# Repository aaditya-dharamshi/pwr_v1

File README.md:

# pwr_v1
Main powerboard (first version) PCB files.

This was the first major board designed for SeeGoals, a project under FIA Robotics at Linkoping University, Sweden. I designed the complete PCB (assisted by other teammates who have developed the foundation), and the design files are shared here with permission from LiU SeeGoals.

This was the prototype for the main power distribution and interface board for the robot, powered by a 23.8V LiPo battery. This board is designed with KiCAD 8, and this repository contains the KiCAD project files and related documents.

# Documentations
📄 [Schematic PDF](Docs%20and%20Images/pwr_v1_schematic.pdf)
📄 [Layout PDF ](Docs%20and%20Images/pwr_v1_CopperLayers.pdf)

# 3D renders
Top view

Bottom view

Main features:
- 3.3V, 5V and 12V buck converters
- IMU on board
- Interfaces for STM32 Nucleo, nRF board and kicker board.

Stackup: 
- 4-layer FR4 PCB with 1.6mm thickness
- Copper thickness: 2 oz outer layer and 1 oz inner layers.

Design considerations:
- High-current power distribution from the LiPo battery.
- Dedicated power and signal layers.
- 4-layered stackup for improved grounding and power integrity.
- Decoupling capacitors placed carefully near the components.
- SMD-type connectors used for STM32 Nucleo interface, reducing thru hole pins and enabling better power and ground plane integrity.

Validation	
- This board was fabricated, assembled and integrated into the robot.
- During validation, issues related to nRF connector pin mapping, connector selection and mechanical design perspectivewere identified, which were addressed in the second revision.

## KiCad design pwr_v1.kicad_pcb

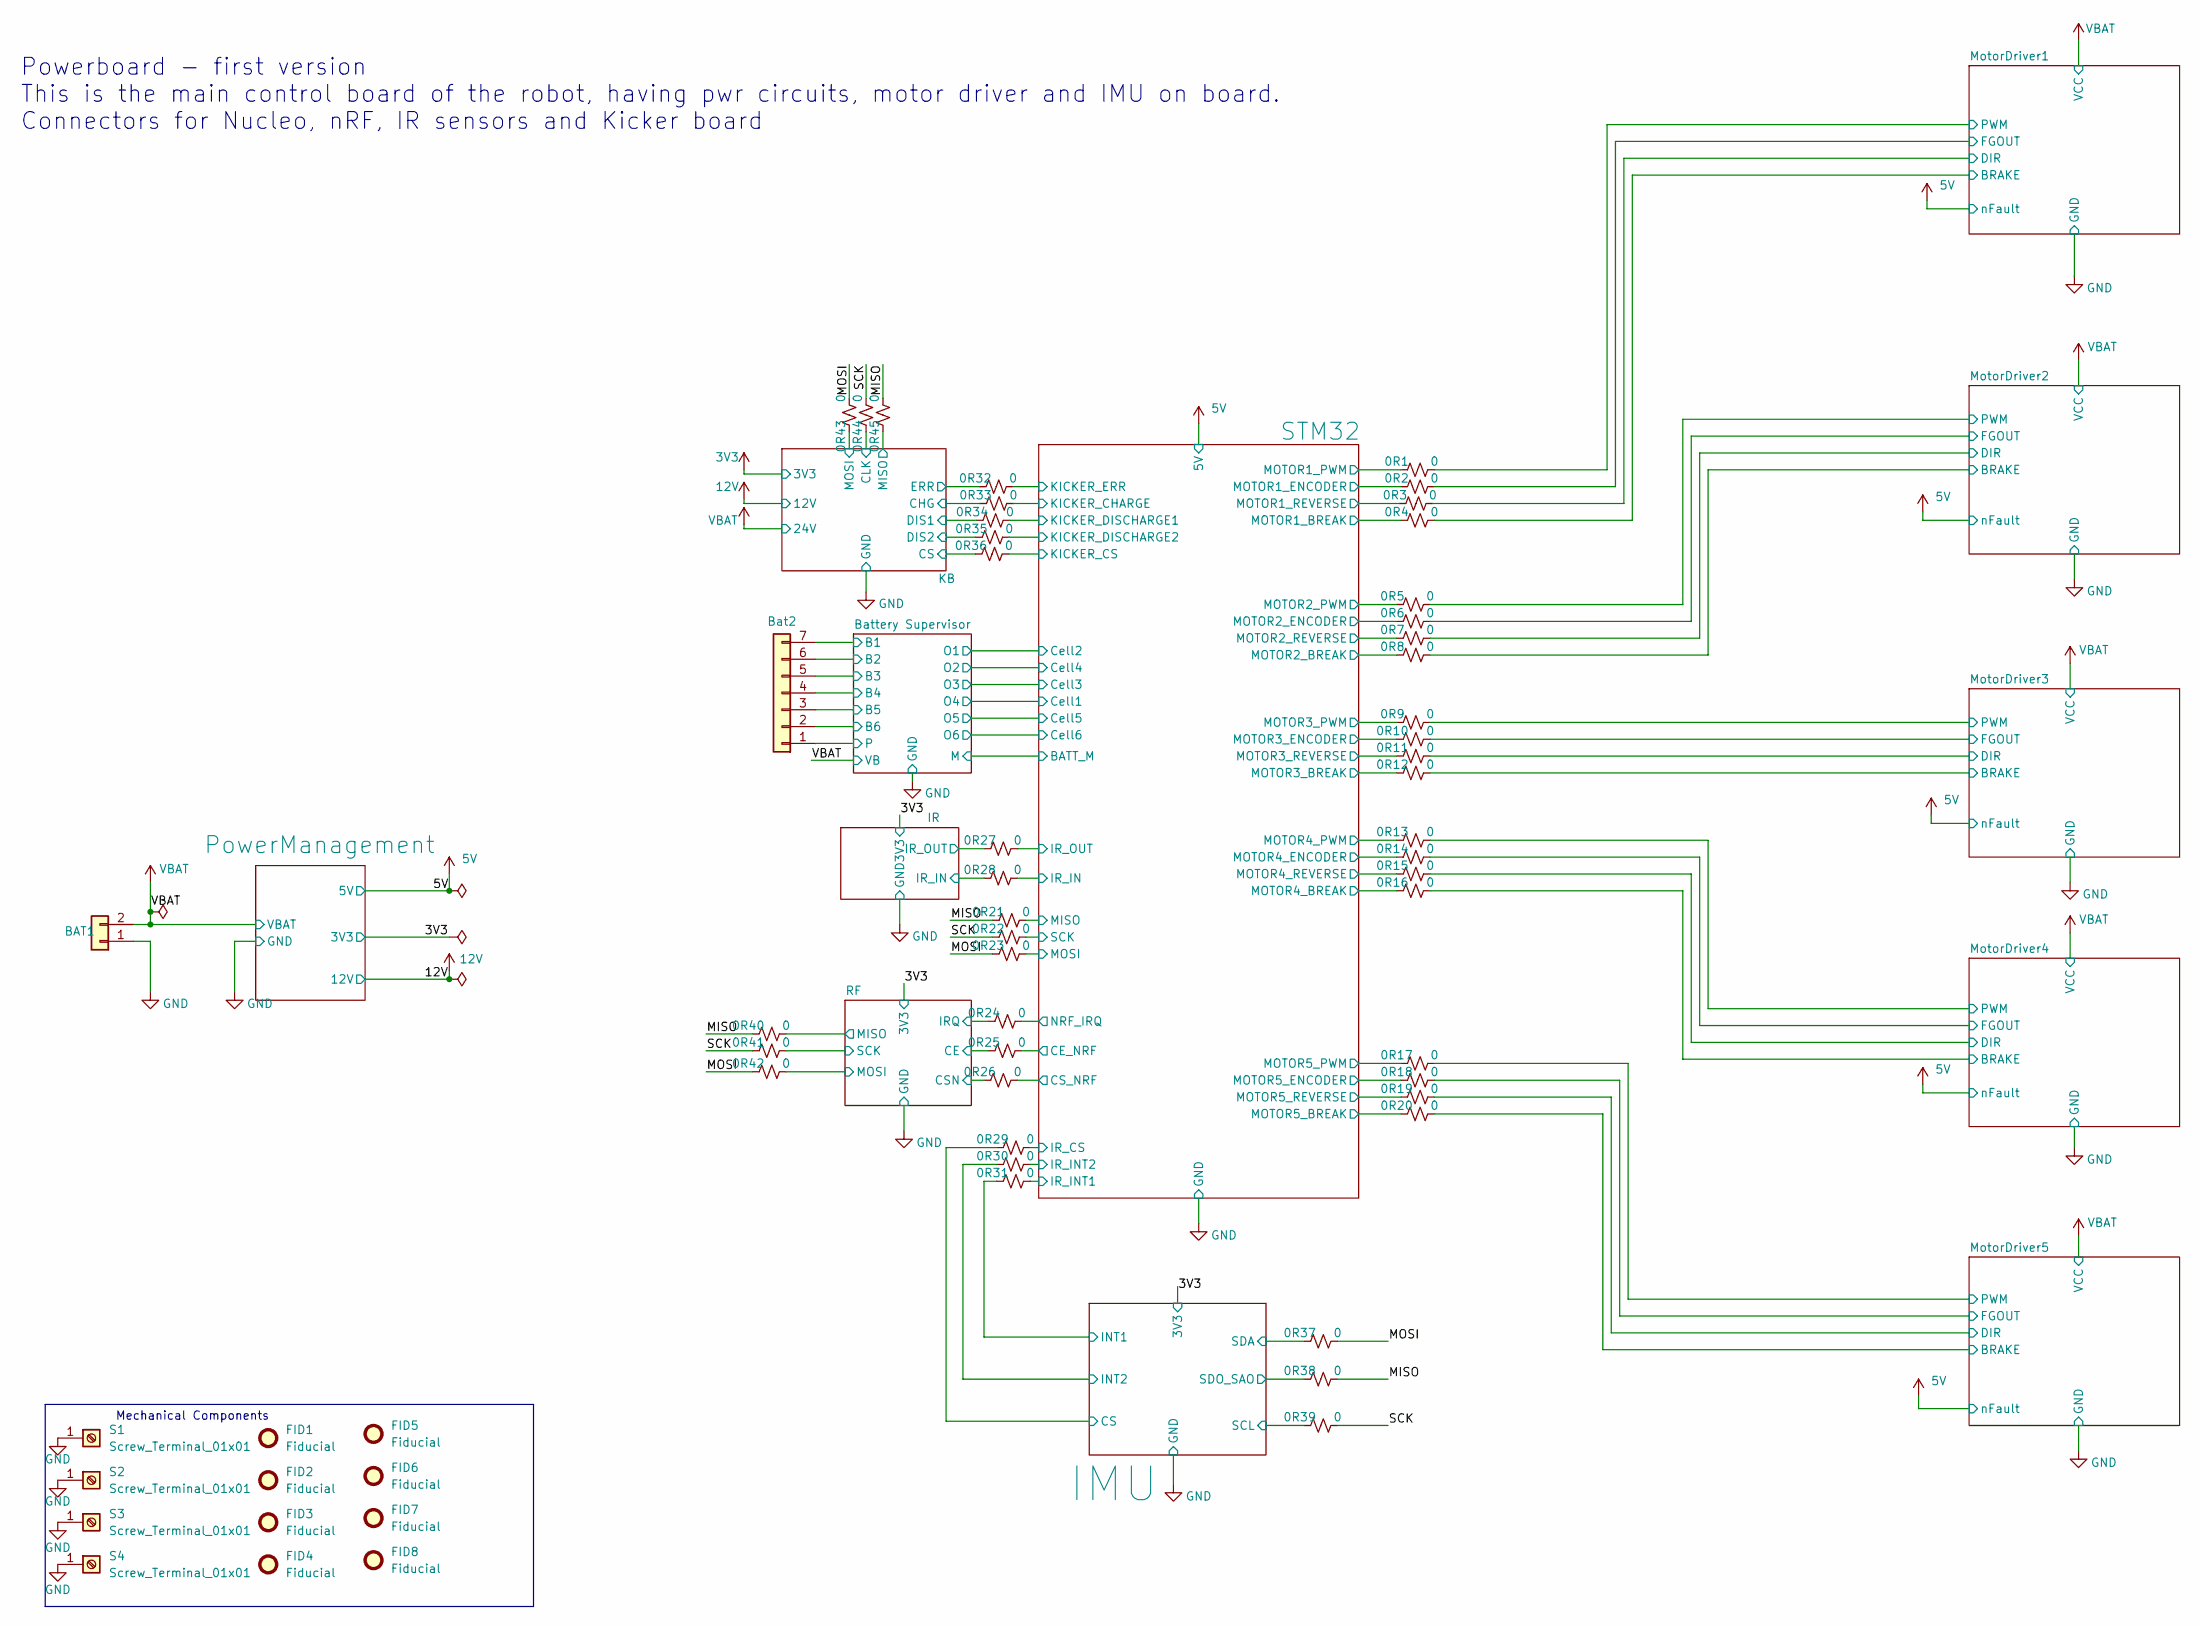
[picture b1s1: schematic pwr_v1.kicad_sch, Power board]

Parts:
0R1, 0R2, 0R3, 0R4, 0R5, 0R6, 0R7, 0R8, 0R9, 0R10, 0R11, 0R12, 0R13, 0R14, 0R15, 0R16, 0R17, 0R18, 0R19, 0R20, 0R21, 0R22, 0R23, 0R24, 0R25, 0R26, 0R27, 0R28, 0R29, 0R30, 0R31, 0R32, 0R33, 0R34, 0R35, 0R36, 0R37, 0R38, 0R39, 0R40, 0R41, 0R42, 0R43, 0R44, 0R45: 0; R_0603_1608Metric
BAT1: XT60; AMASS_XT60-M_1x02_P7.20mm_Vertical
Bat2: Conn_01x07; JST_B7B-XH-A
FID1, FID2, FID3, FID4, FID5, FID6, FID7, FID8: Fiducial; Fiducial_1mm_Mask3mm
S1, S2, S3, S4: Screw_Terminal_01x01; TerminalBlock_MetzConnect_360271_1x01_Horizontal_ScrewM3.0_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

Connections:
/Battery Supervisor/B1: Bat2.7; also elsewhere on the board
/Battery Supervisor/B2: Bat2.6; also elsewhere on the board
/Battery Supervisor/B3: Bat2.5; also elsewhere on the board
/Battery Supervisor/B4: Bat2.4; also elsewhere on the board
/Battery Supervisor/B5: Bat2.3; also elsewhere on the board
/Battery Supervisor/B6: Bat2.2; also elsewhere on the board
/Battery Supervisor/P: Bat2.1; also elsewhere on the board
/IMU/CS: 0R29.1; also elsewhere on the board
/IMU/INT1: 0R31.1; also elsewhere on the board
/IMU/INT2: 0R30.1; also elsewhere on the board
/IMU/SCL: 0R39.1; also elsewhere on the board
/IMU/SDA: 0R37.1; also elsewhere on the board
/IMU/SDO_SAO: 0R38.1; also elsewhere on the board
/IR/IR_IN: 0R28.1; also elsewhere on the board
/IR/IR_OUT: 0R27.1; also elsewhere on the board
/KB/CHG: 0R33.1; also elsewhere on the board
/KB/CLK: 0R44.1; also elsewhere on the board
/KB/CS: 0R36.1; also elsewhere on the board
/KB/DIS1: 0R34.1; also elsewhere on the board
/KB/DIS2: 0R35.1; also elsewhere on the board
/KB/ERR: 0R32.1; also elsewhere on the board
/KB/MISO: 0R45.1; also elsewhere on the board
/KB/MOSI: 0R43.1; also elsewhere on the board
/MISO: 0R21.1, 0R38.2, 0R40.1, 0R45.2
/MOSI: 0R23.1, 0R37.2, 0R42.1, 0R43.2
/MotorDriver1/BRAKE: 0R4.2; also elsewhere on the board
/MotorDriver1/DIR: 0R3.2; also elsewhere on the board
/MotorDriver1/FGOUT: 0R2.2; also elsewhere on the board
/MotorDriver1/PWM: 0R1.2; also elsewhere on the board
/MotorDriver2/BRAKE: 0R8.2; also elsewhere on the board
/MotorDriver2/DIR: 0R7.2; also elsewhere on the board
/MotorDriver2/FGOUT: 0R6.2; also elsewhere on the board
/MotorDriver2/PWM: 0R5.2; also elsewhere on the board
/MotorDriver3/BRAKE: 0R12.2; also elsewhere on the board
/MotorDriver3/DIR: 0R11.2; also elsewhere on the board
/MotorDriver3/FGOUT: 0R10.2; also elsewhere on the board
/MotorDriver3/PWM: 0R9.2; also elsewhere on the board
/MotorDriver4/BRAKE: 0R16.2; also elsewhere on the board
/MotorDriver4/DIR: 0R15.2; also elsewhere on the board
/MotorDriver4/FGOUT: 0R14.2; also elsewhere on the board
/MotorDriver4/PWM: 0R13.2; also elsewhere on the board
/MotorDriver5/BRAKE: 0R20.2; also elsewhere on the board
/MotorDriver5/DIR: 0R19.2; also elsewhere on the board
/MotorDriver5/FGOUT: 0R18.2; also elsewhere on the board
/MotorDriver5/PWM: 0R17.2; also elsewhere on the board
/RF/CE: 0R25.1; also elsewhere on the board
/RF/CSN: 0R26.1; also elsewhere on the board
/RF/IRQ: 0R24.1; also elsewhere on the board
/RF/MISO: 0R40.2; also elsewhere on the board
/RF/MOSI: 0R42.2; also elsewhere on the board
/RF/SCK: 0R41.2; also elsewhere on the board
/SCK: 0R22.1, 0R39.2, 0R41.1, 0R44.2
/STM32/CE_NRF: 0R25.2; also elsewhere on the board
/STM32/CS_NRF: 0R26.2; also elsewhere on the board
/STM32/IR_CS: 0R29.2; also elsewhere on the board
/STM32/IR_IN: 0R28.2; also elsewhere on the board
/STM32/IR_INT1: 0R31.2; also elsewhere on the board
/STM32/IR_INT2: 0R30.2; also elsewhere on the board
/STM32/IR_OUT: 0R27.2; also elsewhere on the board
/STM32/KICKER_CHARGE: 0R33.2; also elsewhere on the board
/STM32/KICKER_CS: 0R36.2; also elsewhere on the board
/STM32/KICKER_DISCHARGE1: 0R34.2; also elsewhere on the board
/STM32/KICKER_DISCHARGE2: 0R35.2; also elsewhere on the board
/STM32/KICKER_ERR: 0R32.2; also elsewhere on the board
/STM32/MISO: 0R21.2; also elsewhere on the board
/STM32/MOSI: 0R23.2; also elsewhere on the board
/STM32/MOTOR1_BREAK: 0R4.1; also elsewhere on the board
/STM32/MOTOR1_ENCODER: 0R2.1; also elsewhere on the board
/STM32/MOTOR1_PWM: 0R1.1; also elsewhere on the board
/STM32/MOTOR1_REVERSE: 0R3.1; also elsewhere on the board
/STM32/MOTOR2_BREAK: 0R8.1; also elsewhere on the board
/STM32/MOTOR2_ENCODER: 0R6.1; also elsewhere on the board
/STM32/MOTOR2_PWM: 0R5.1; also elsewhere on the board
/STM32/MOTOR2_REVERSE: 0R7.1; also elsewhere on the board
/STM32/MOTOR3_BREAK: 0R12.1; also elsewhere on the board
/STM32/MOTOR3_ENCODER: 0R10.1; also elsewhere on the board
/STM32/MOTOR3_PWM: 0R9.1; also elsewhere on the board
/STM32/MOTOR3_REVERSE: 0R11.1; also elsewhere on the board
/STM32/MOTOR4_BREAK: 0R16.1; also elsewhere on the board
/STM32/MOTOR4_ENCODER: 0R14.1; also elsewhere on the board
/STM32/MOTOR4_PWM: 0R13.1; also elsewhere on the board
/STM32/MOTOR4_REVERSE: 0R15.1; also elsewhere on the board
/STM32/MOTOR5_BREAK: 0R20.1; also elsewhere on the board
/STM32/MOTOR5_ENCODER: 0R18.1; also elsewhere on the board
/STM32/MOTOR5_PWM: 0R17.1; also elsewhere on the board
/STM32/MOTOR5_REVERSE: 0R19.1; also elsewhere on the board
/STM32/NRF_IRQ: 0R24.2; also elsewhere on the board
/STM32/SCK: 0R22.2; also elsewhere on the board
GND: BAT1.1, S1.1, S2.1, S3.1, S4.1; also elsewhere on the board
VBAT: BAT1.2; also elsewhere on the board

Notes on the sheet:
Mechanical Components
Powerboard - first version This is the main control board of the robot, having pwr circuits, motor driver and IMU on board. Connectors for Nucleo, nRF, IR sensors and Kicker board

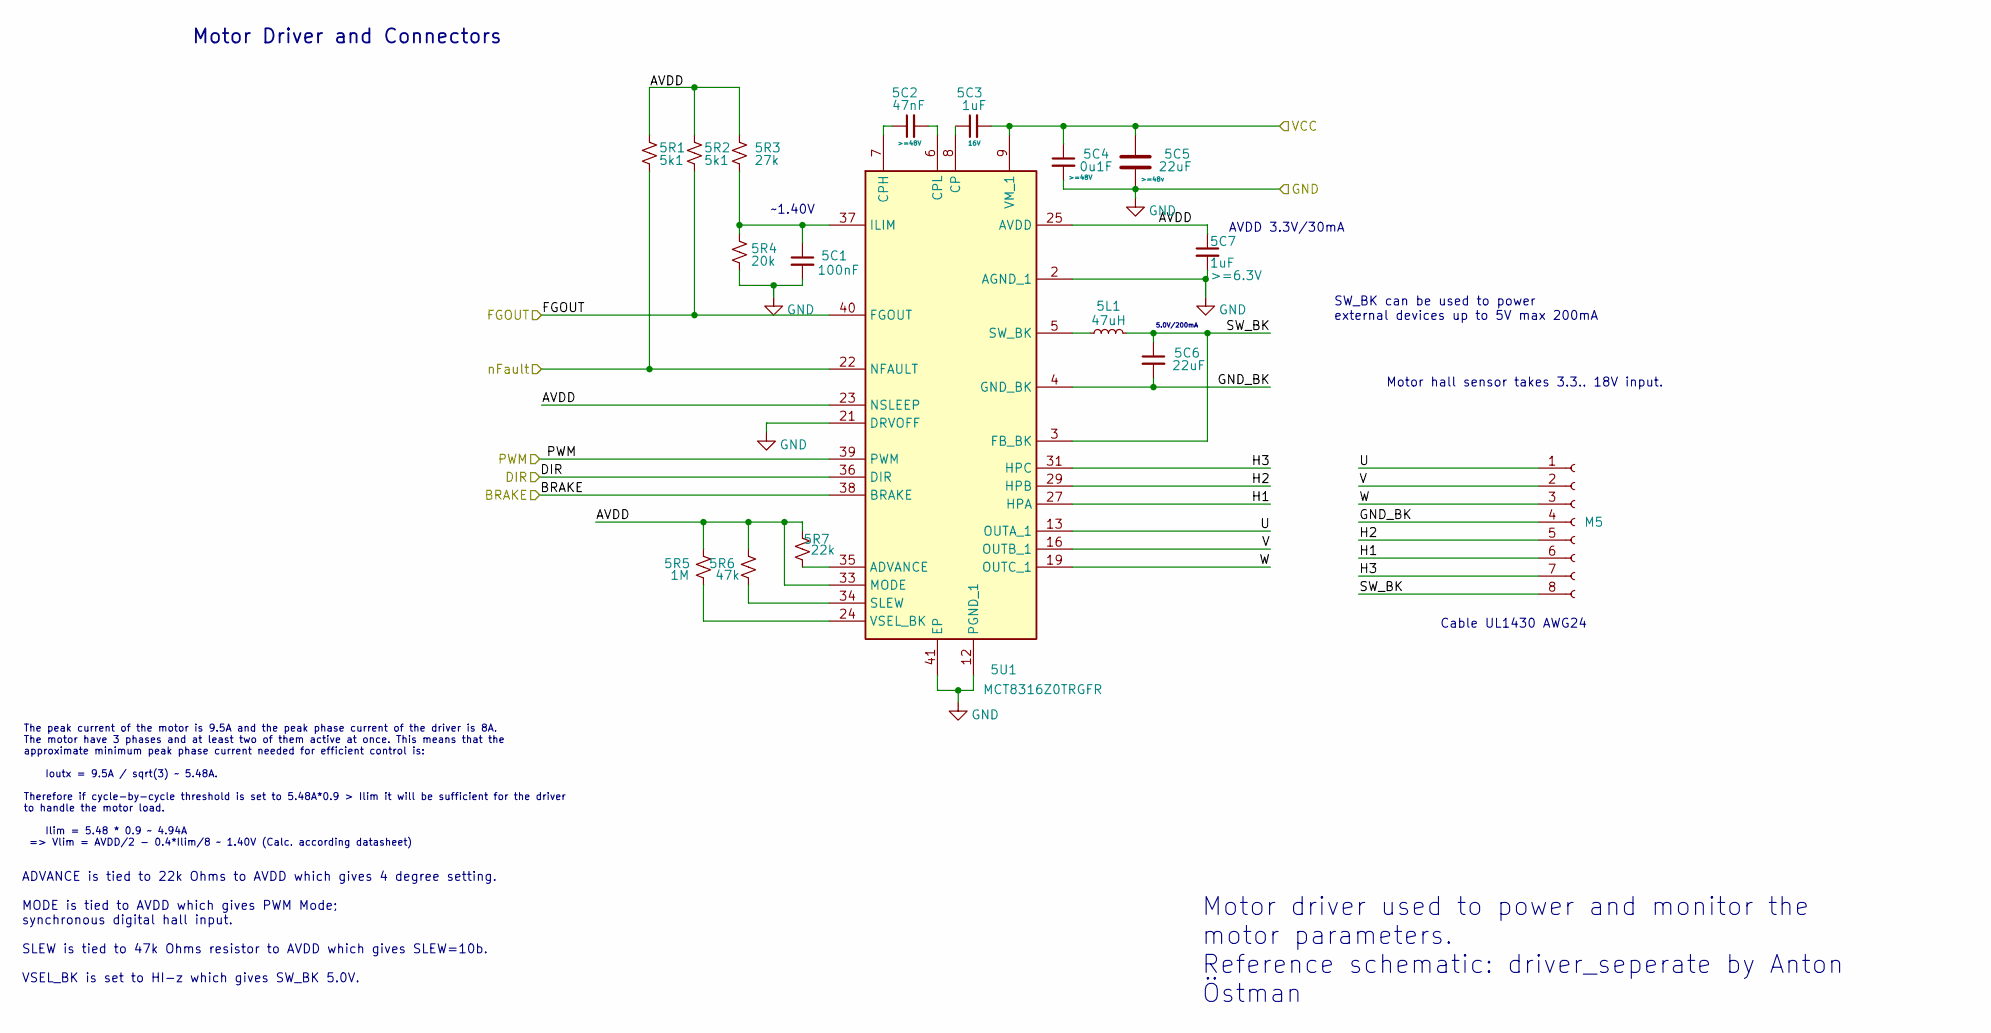
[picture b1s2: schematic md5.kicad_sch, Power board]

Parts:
5C1: 100nF; C_0402_1005Metric
5C2: 47nF; C_0402_1005Metric; Voltage >=48V
5C3: 1uF; C_0402_1005Metric; Voltage 16V
5C4: 0u1F; C_0402_1005Metric; Voltage >=48V
5C5: 22uF; C_2220_5750Metric; Voltage >=48v
5C6: 22uF; C_0402_1005Metric
5C7: 1uF; C_0402_1005Metric; Voltage >=6.3V
5L1: 47uH; L_0805_2012Metric
5R1, 5R2: 5k1; R_0603_1608Metric
5R3: 27k; R_0603_1608Metric
5R4: 20k; R_0603_1608Metric
5R5: 1M; R_0805_2012Metric
5R6: 47k; R_0402_1005Metric
5R7: 22k; R_0402_1005Metric
5U1: MCT8316Z0TRGFR; RGF0040E-IPC_B; Mouser Part Number 595-CT8316Z0TQRGFRQ1
M5: Conn_01x08_Socket; PinHeader_1x08_P2.54mm_Vertical

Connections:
5V: 5R1.2, 5U1.22 (NFAULT); also elsewhere on the board
/MotorDriver5/AVDD: 5C7.1, 5R1.1, 5R2.1, 5R3.1, 5R5.2, 5R6.2, 5R7.2, 5U1.23 (NSLEEP), 5U1.25 (AVDD), 5U1.33 (MODE)
/MotorDriver5/BRAKE: 5U1.38 (BRAKE); also elsewhere on the board
/MotorDriver5/DIR: 5U1.36 (DIR); also elsewhere on the board
/MotorDriver5/FGOUT: 5R2.2, 5U1.40 (FGOUT); also elsewhere on the board
/MotorDriver5/GND_BK: 5C6.2, 5U1.4 (GND_BK), M5.4
/MotorDriver5/H1: 5U1.27 (HPA), M5.6
/MotorDriver5/H2: 5U1.29 (HPB), M5.5
/MotorDriver5/H3: 5U1.31 (HPC), M5.7
/MotorDriver5/PWM: 5U1.39 (PWM); also elsewhere on the board
/MotorDriver5/SW_BK: 5C6.1, 5L1.2, 5U1.3 (FB_BK), M5.8
/MotorDriver5/U: 5U1.13 (OUTA_1), 5U1.14 (OUTA_2), M5.1
/MotorDriver5/V: 5U1.16 (OUTB_1), 5U1.17 (OUTB_2), M5.2
/MotorDriver5/W: 5U1.19 (OUTC_1), 5U1.20 (OUTC_2), M5.3
GND: 5C1.2, 5C4.2, 5C5.2, 5C7.2, 5R4.2, 5U1.2 (AGND_1), 5U1.12 (PGND_1), 5U1.15 (PGND_2), 5U1.18 (PGND_3), 5U1.21 (DRVOFF), 5U1.26 (AGND_2), 5U1.41 (EP); also elsewhere on the board
unnamed: 5R7.1, 5U1.35 (ADVANCE)
unnamed: 5C3.1, 5U1.8 (CP)
unnamed: 5C2.1, 5U1.7 (CPH)
unnamed: 5C2.2, 5U1.6 (CPL)
unnamed: 5C1.1, 5R3.2, 5R4.1, 5U1.37 (ILIM)
unnamed: 5R6.1, 5U1.34 (SLEW)
unnamed: 5L1.1, 5U1.5 (SW_BK)
unnamed: 5R5.1, 5U1.24 (VSEL_BK)
VBAT: 5C3.2, 5C4.1, 5C5.1, 5U1.9 (VM_1), 5U1.10 (VM_2), 5U1.11 (VM_3); also elsewhere on the board

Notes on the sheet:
SW_BK can be used to power external devices up to 5V max 200mA
5.0V/200mA
Cable UL1430 AWG24
ADVANCE is tied to 22k Ohms to AVDD which gives 4 degree setting. MODE is tied to AVDD which gives PWM Mode; synchronous digital hall input. SLEW is tied to 47k Ohms resistor to AVDD which gives SLEW=10b. VSEL_BK is set to HI-z which gives SW_BK 5.0V.
~1.40V
AVDD 3.3V/30mA
Motor Driver and Connectors
Motor hall sensor takes 3.3.. 18V input.
The peak current of the motor is 9.5A and the peak phase current of the driver is 8A. The motor have 3 phases and at least two of them active at once. This means that the approximate minimum peak phase current needed for efficient control is: Ioutx = 9.5A / sqrt(3) ~ 5.48A. Therefore if cycle-by-cy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
Motor driver used to power and monitor the motor parameters. Reference schematic: driver_seperate by Anton Östman

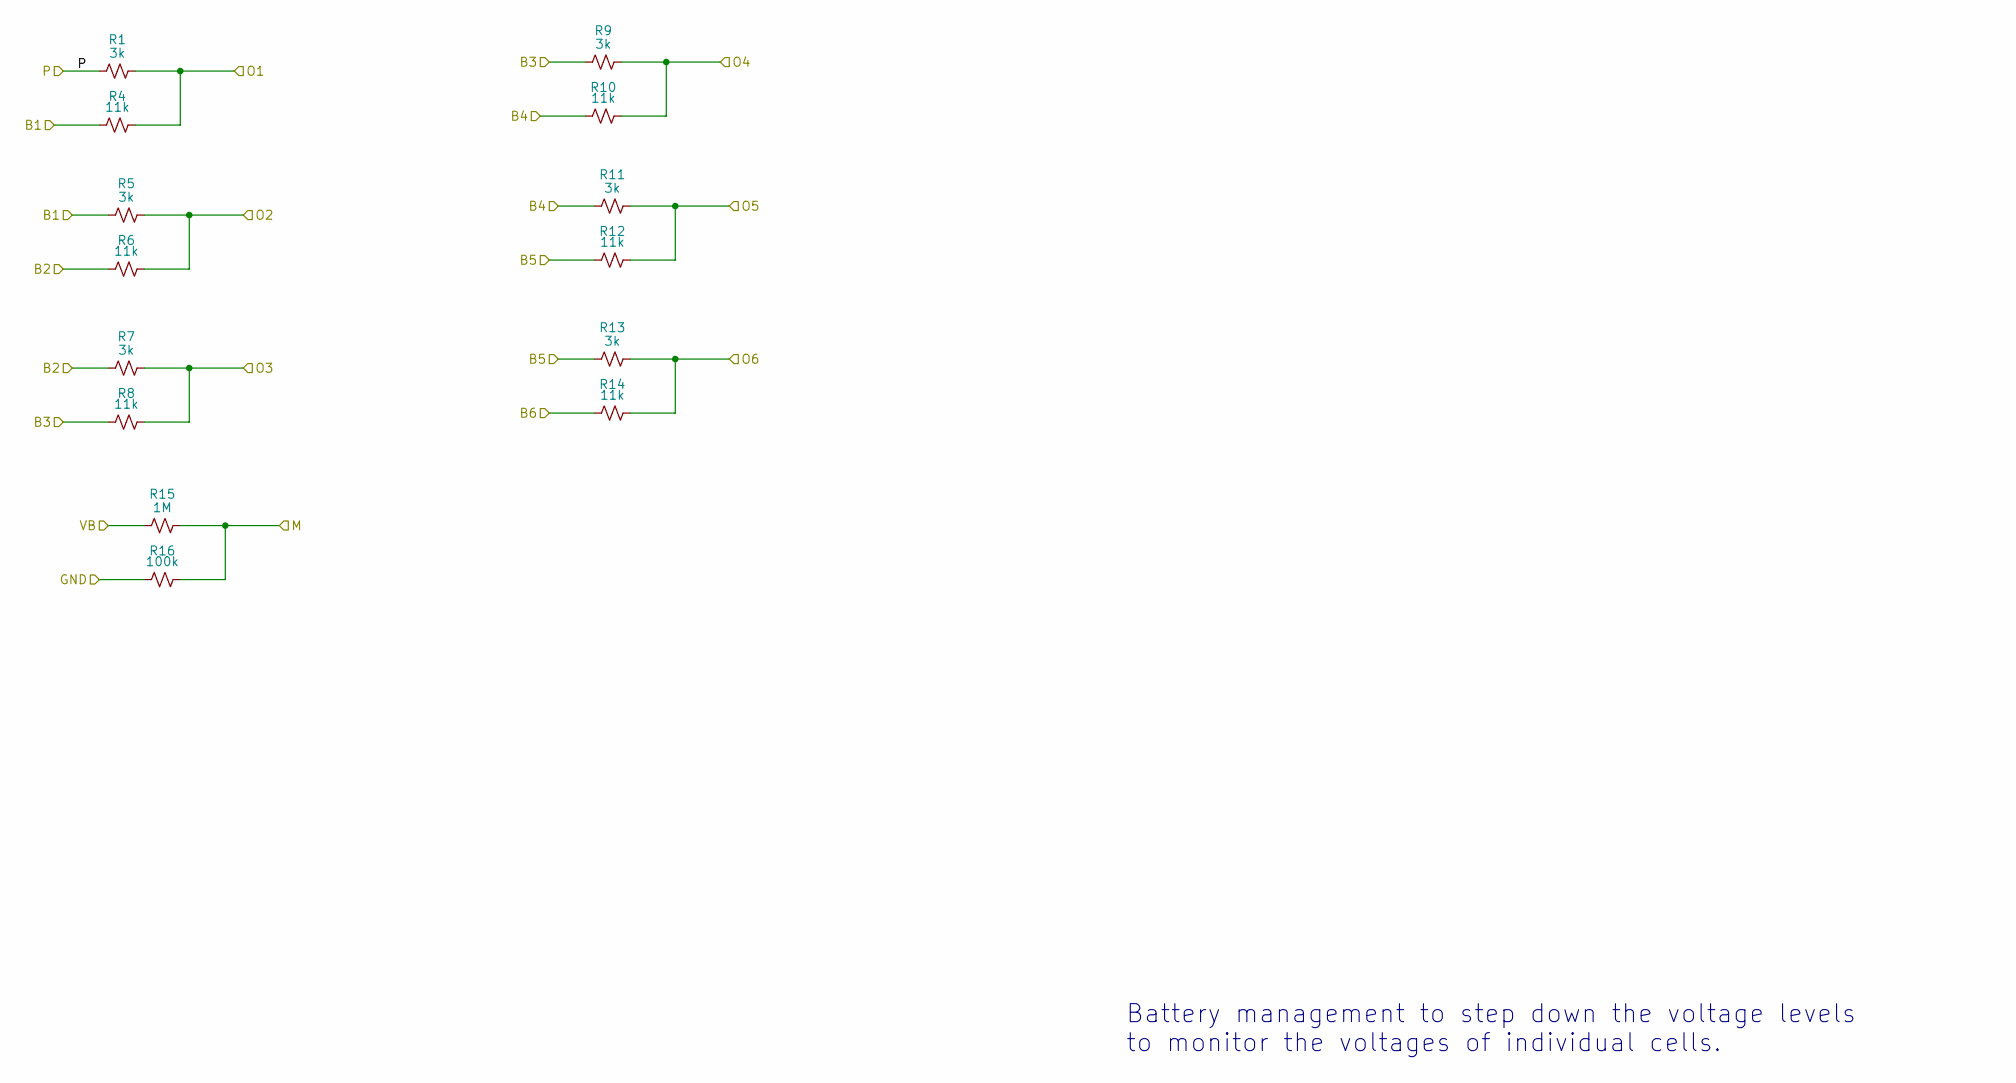
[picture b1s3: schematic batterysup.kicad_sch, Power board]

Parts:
R1, R5, R7, R9, R11, R13: 3k; R_0402_1005Metric
R4, R6, R8, R10, R12, R14: 11k; R_0402_1005Metric
R15: 1M; R_0603_1608Metric
R16: 100k; R_0603_1608Metric

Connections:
/Battery Supervisor/B1: R4.1, R5.1; also elsewhere on the board
/Battery Supervisor/B2: R6.1, R7.1; also elsewhere on the board
/Battery Supervisor/B3: R8.1, R9.1; also elsewhere on the board
/Battery Supervisor/B4: R10.1, R11.1; also elsewhere on the board
/Battery Supervisor/B5: R12.1, R13.1; also elsewhere on the board
/Battery Supervisor/B6: R14.1; also elsewhere on the board
/Battery Supervisor/M: R15.2, R16.2; also elsewhere on the board
/Battery Supervisor/O1: R1.2, R4.2; also elsewhere on the board
/Battery Supervisor/O2: R5.2, R6.2; also elsewhere on the board
/Battery Supervisor/O3: R7.2, R8.2; also elsewhere on the board
/Battery Supervisor/O4: R9.2, R10.2; also elsewhere on the board
/Battery Supervisor/O5: R11.2, R12.2; also elsewhere on the board
/Battery Supervisor/O6: R13.2, R14.2; also elsewhere on the board
/Battery Supervisor/P: R1.1; also elsewhere on the board
GND: R16.1; also elsewhere on the board
VBAT: R15.1; also elsewhere on the board

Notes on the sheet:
Battery management to step down the voltage levels to monitor the voltages of individual cells.

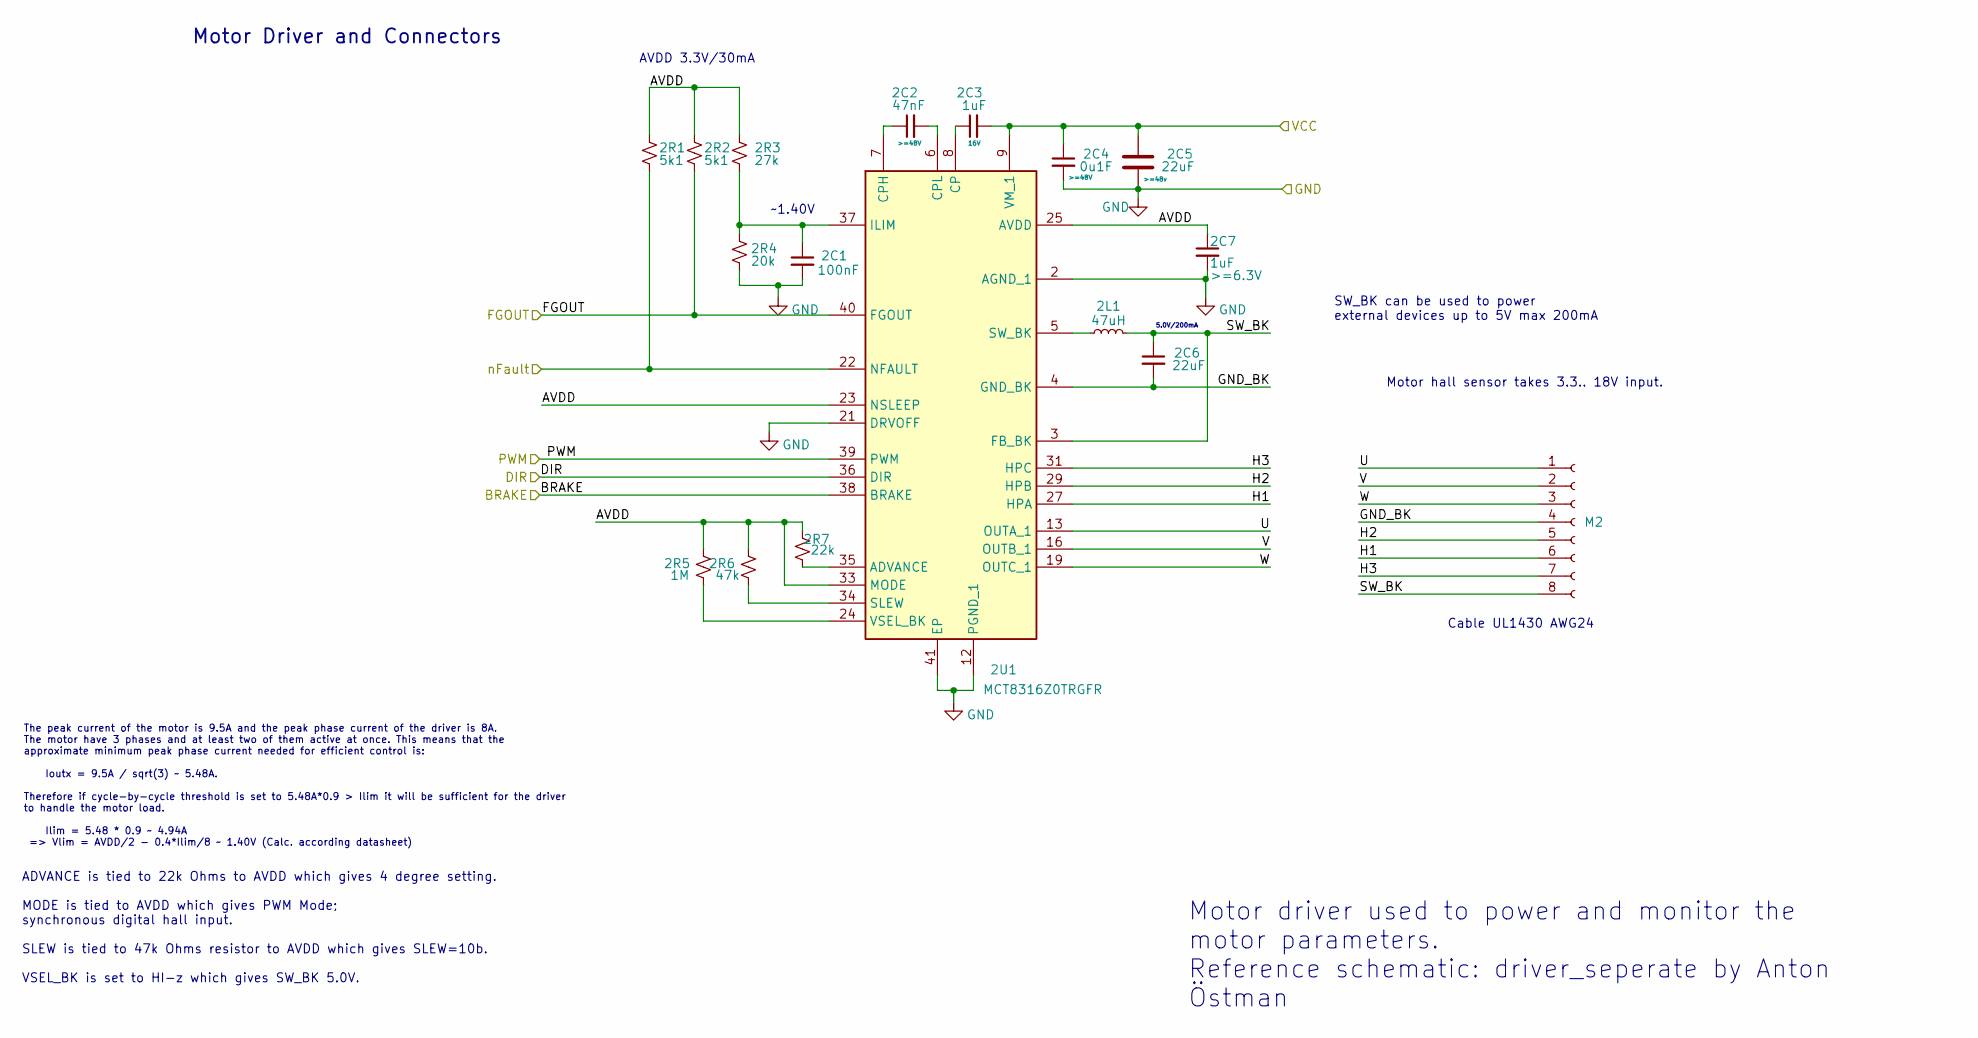
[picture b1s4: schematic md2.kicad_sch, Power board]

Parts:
2C1: 100nF; C_0402_1005Metric
2C2: 47nF; C_0402_1005Metric; Voltage >=48V
2C3: 1uF; C_0402_1005Metric; Voltage 16V
2C4: 0u1F; C_0402_1005Metric; Voltage >=48V
2C5: 22uF; C_2220_5750Metric; Voltage >=48v
2C6: 22uF; C_0402_1005Metric
2C7: 1uF; C_0402_1005Metric; Voltage >=6.3V
2L1: 47uH; L_0805_2012Metric
2R1, 2R2: 5k1; R_0603_1608Metric
2R3: 27k; R_0603_1608Metric
2R4: 20k; R_0603_1608Metric
2R5: 1M; R_0805_2012Metric
2R6: 47k; R_0402_1005Metric
2R7: 22k; R_0402_1005Metric
2U1: MCT8316Z0TRGFR; RGF0040E-IPC_B; Mouser Part Number 595-CT8316Z0TQRGFRQ1
M2: Conn_01x08_Socket; PinHeader_1x08_P2.54mm_Vertical

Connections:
5V: 2R1.2, 2U1.22 (NFAULT); also elsewhere on the board
/MotorDriver2/AVDD: 2C7.1, 2R1.1, 2R2.1, 2R3.1, 2R5.2, 2R6.2, 2R7.2, 2U1.23 (NSLEEP), 2U1.25 (AVDD), 2U1.33 (MODE)
/MotorDriver2/BRAKE: 2U1.38 (BRAKE); also elsewhere on the board
/MotorDriver2/DIR: 2U1.36 (DIR); also elsewhere on the board
/MotorDriver2/FGOUT: 2R2.2, 2U1.40 (FGOUT); also elsewhere on the board
/MotorDriver2/GND_BK: 2C6.2, 2U1.4 (GND_BK), M2.4
/MotorDriver2/H1: 2U1.27 (HPA), M2.6
/MotorDriver2/H2: 2U1.29 (HPB), M2.5
/MotorDriver2/H3: 2U1.31 (HPC), M2.7
/MotorDriver2/PWM: 2U1.39 (PWM); also elsewhere on the board
/MotorDriver2/SW_BK: 2C6.1, 2L1.2, 2U1.3 (FB_BK), M2.8
/MotorDriver2/U: 2U1.13 (OUTA_1), 2U1.14 (OUTA_2), M2.1
/MotorDriver2/V: 2U1.16 (OUTB_1), 2U1.17 (OUTB_2), M2.2
/MotorDriver2/W: 2U1.19 (OUTC_1), 2U1.20 (OUTC_2), M2.3
GND: 2C1.2, 2C4.2, 2C5.2, 2C7.2, 2R4.2, 2U1.2 (AGND_1), 2U1.12 (PGND_1), 2U1.15 (PGND_2), 2U1.18 (PGND_3), 2U1.21 (DRVOFF), 2U1.26 (AGND_2), 2U1.41 (EP); also elsewhere on the board
unnamed: 2R7.1, 2U1.35 (ADVANCE)
unnamed: 2C3.1, 2U1.8 (CP)
unnamed: 2C2.1, 2U1.7 (CPH)
unnamed: 2C2.2, 2U1.6 (CPL)
unnamed: 2C1.1, 2R3.2, 2R4.1, 2U1.37 (ILIM)
unnamed: 2R6.1, 2U1.34 (SLEW)
unnamed: 2L1.1, 2U1.5 (SW_BK)
unnamed: 2R5.1, 2U1.24 (VSEL_BK)
VBAT: 2C3.2, 2C4.1, 2C5.1, 2U1.9 (VM_1), 2U1.10 (VM_2), 2U1.11 (VM_3); also elsewhere on the board

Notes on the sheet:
SW_BK can be used to power external devices up to 5V max 200mA
ADVANCE is tied to 22k Ohms to AVDD which gives 4 degree setting. MODE is tied to AVDD which gives PWM Mode; synchronous digital hall input. SLEW is tied to 47k Ohms resistor to AVDD which gives SLEW=10b. VSEL_BK is set to HI-z which gives SW_BK 5.0V.
~1.40V
Motor Driver and Connectors
Cable UL1430 AWG24
AVDD 3.3V/30mA
The peak current of the motor is 9.5A and the peak phase current of the driver is 8A. The motor have 3 phases and at least two of them active at once. This means that the approximate minimum peak phase current needed for efficient control is: Ioutx = 9.5A / sqrt(3) ~ 5.48A. Therefore if cycle-by-cy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
Motor hall sensor takes 3.3.. 18V input.
5.0V/200mA
Motor driver used to power and monitor the motor parameters. Reference schematic: driver_seperate by Anton Östman

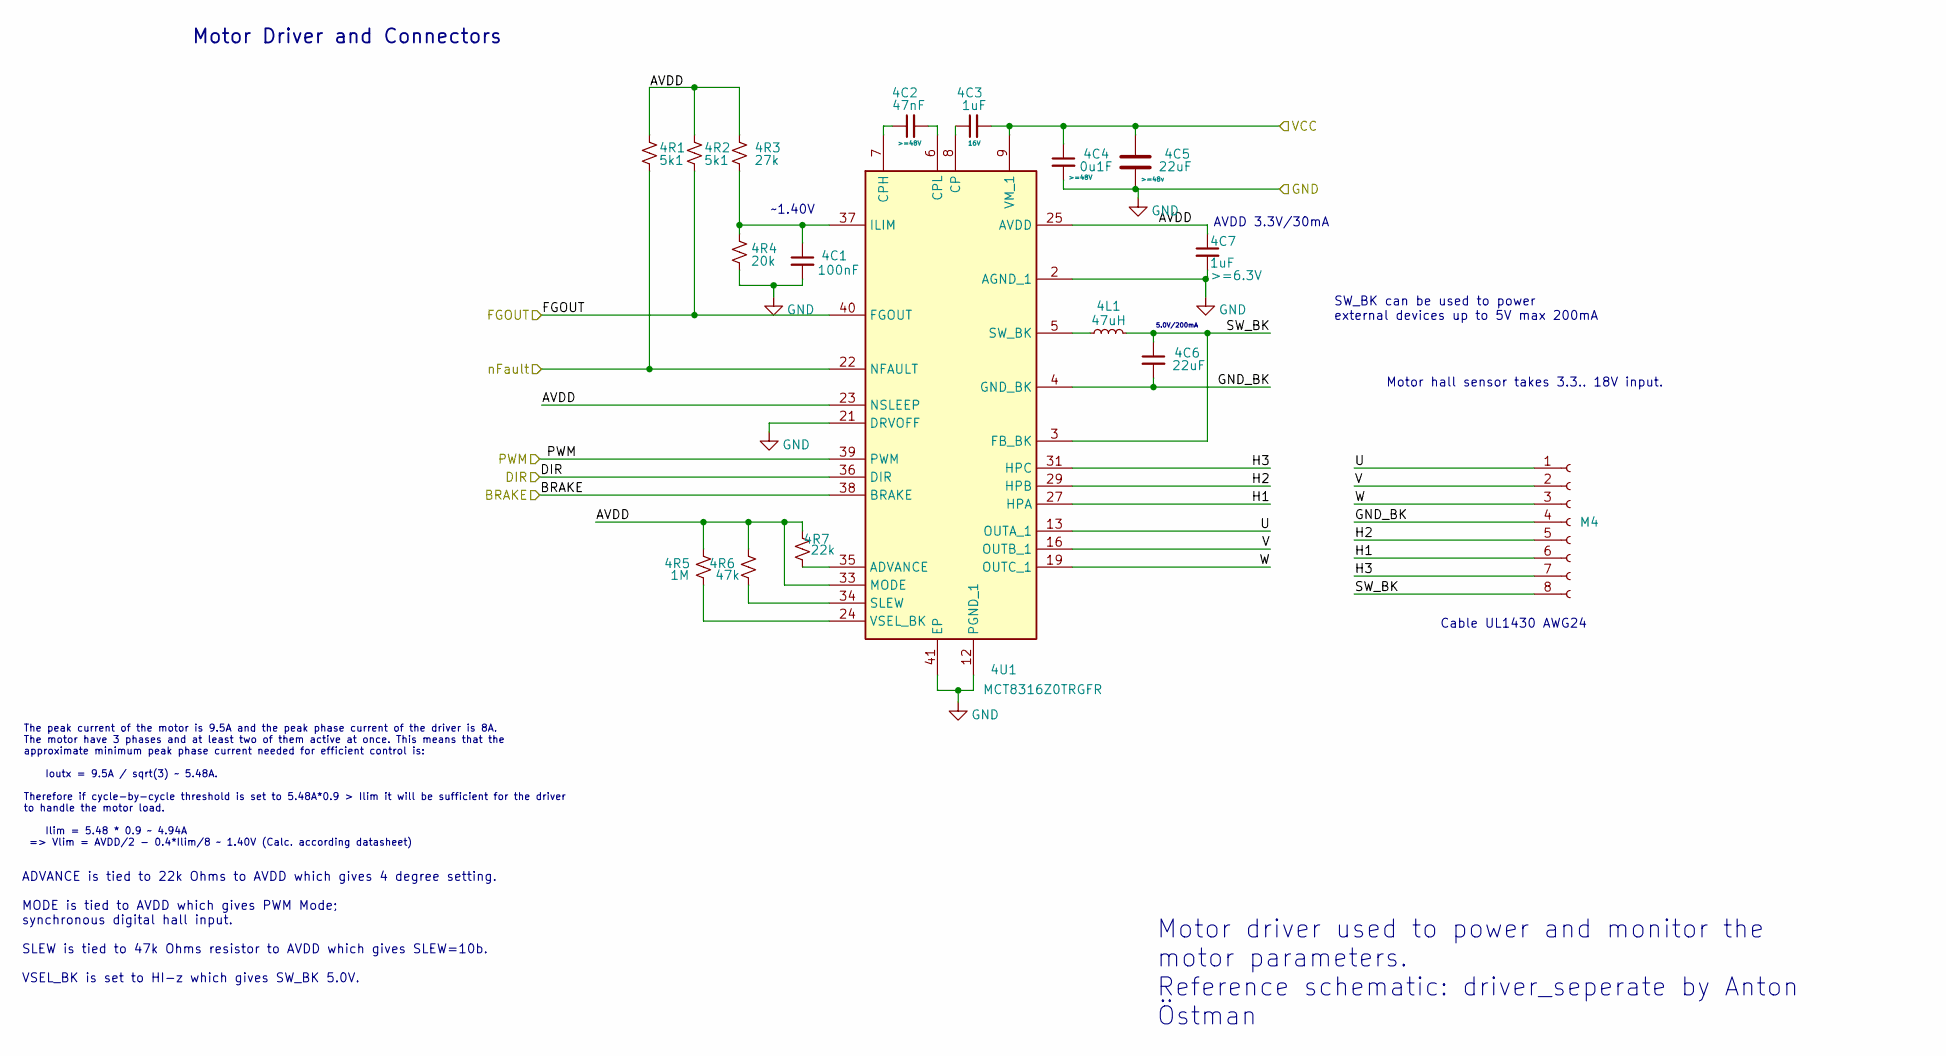
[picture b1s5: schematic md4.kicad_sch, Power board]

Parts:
4C1: 100nF; C_0402_1005Metric
4C2: 47nF; C_0402_1005Metric; Voltage >=48V
4C3: 1uF; C_0402_1005Metric; Voltage 16V
4C4: 0u1F; C_0402_1005Metric; Voltage >=48V
4C5: 22uF; C_2220_5750Metric; Voltage >=48v
4C6: 22uF; C_0402_1005Metric
4C7: 1uF; C_0402_1005Metric; Voltage >=6.3V
4L1: 47uH; L_0805_2012Metric
4R1, 4R2: 5k1; R_0603_1608Metric
4R3: 27k; R_0603_1608Metric
4R4: 20k; R_0603_1608Metric
4R5: 1M; R_0805_2012Metric
4R6: 47k; R_0402_1005Metric
4R7: 22k; R_0402_1005Metric
4U1: MCT8316Z0TRGFR; RGF0040E-IPC_B; Mouser Part Number 595-CT8316Z0TQRGFRQ1
M4: Conn_01x08_Socket; PinHeader_1x08_P2.54mm_Vertical

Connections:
5V: 4R1.2, 4U1.22 (NFAULT); also elsewhere on the board
/MotorDriver4/AVDD: 4C7.1, 4R1.1, 4R2.1, 4R3.1, 4R5.2, 4R6.2, 4R7.2, 4U1.23 (NSLEEP), 4U1.25 (AVDD), 4U1.33 (MODE)
/MotorDriver4/BRAKE: 4U1.38 (BRAKE); also elsewhere on the board
/MotorDriver4/DIR: 4U1.36 (DIR); also elsewhere on the board
/MotorDriver4/FGOUT: 4R2.2, 4U1.40 (FGOUT); also elsewhere on the board
/MotorDriver4/GND_BK: 4C6.2, 4U1.4 (GND_BK), M4.4
/MotorDriver4/H1: 4U1.27 (HPA), M4.6
/MotorDriver4/H2: 4U1.29 (HPB), M4.5
/MotorDriver4/H3: 4U1.31 (HPC), M4.7
/MotorDriver4/PWM: 4U1.39 (PWM); also elsewhere on the board
/MotorDriver4/SW_BK: 4C6.1, 4L1.2, 4U1.3 (FB_BK), M4.8
/MotorDriver4/U: 4U1.13 (OUTA_1), 4U1.14 (OUTA_2), M4.1
/MotorDriver4/V: 4U1.16 (OUTB_1), 4U1.17 (OUTB_2), M4.2
/MotorDriver4/W: 4U1.19 (OUTC_1), 4U1.20 (OUTC_2), M4.3
GND: 4C1.2, 4C4.2, 4C5.2, 4C7.2, 4R4.2, 4U1.2 (AGND_1), 4U1.12 (PGND_1), 4U1.15 (PGND_2), 4U1.18 (PGND_3), 4U1.21 (DRVOFF), 4U1.26 (AGND_2), 4U1.41 (EP); also elsewhere on the board
unnamed: 4R7.1, 4U1.35 (ADVANCE)
unnamed: 4C3.1, 4U1.8 (CP)
unnamed: 4C2.1, 4U1.7 (CPH)
unnamed: 4C2.2, 4U1.6 (CPL)
unnamed: 4C1.1, 4R3.2, 4R4.1, 4U1.37 (ILIM)
unnamed: 4R6.1, 4U1.34 (SLEW)
unnamed: 4L1.1, 4U1.5 (SW_BK)
unnamed: 4R5.1, 4U1.24 (VSEL_BK)
VBAT: 4C3.2, 4C4.1, 4C5.1, 4U1.9 (VM_1), 4U1.10 (VM_2), 4U1.11 (VM_3); also elsewhere on the board

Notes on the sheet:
Cable UL1430 AWG24
ADVANCE is tied to 22k Ohms to AVDD which gives 4 degree setting. MODE is tied to AVDD which gives PWM Mode; synchronous digital hall input. SLEW is tied to 47k Ohms resistor to AVDD which gives SLEW=10b. VSEL_BK is set to HI-z which gives SW_BK 5.0V.
The peak current of the motor is 9.5A and the peak phase current of the driver is 8A. The motor have 3 phases and at least two of them active at once. This means that the approximate minimum peak phase current needed for efficient control is: Ioutx = 9.5A / sqrt(3) ~ 5.48A. Therefore if cycle-by-cy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
AVDD 3.3V/30mA
Motor hall sensor takes 3.3.. 18V input.
5.0V/200mA
~1.40V
SW_BK can be used to power external devices up to 5V max 200mA
Motor Driver and Connectors
Motor driver used to power and monitor the motor parameters. Reference schematic: driver_seperate by Anton Östman

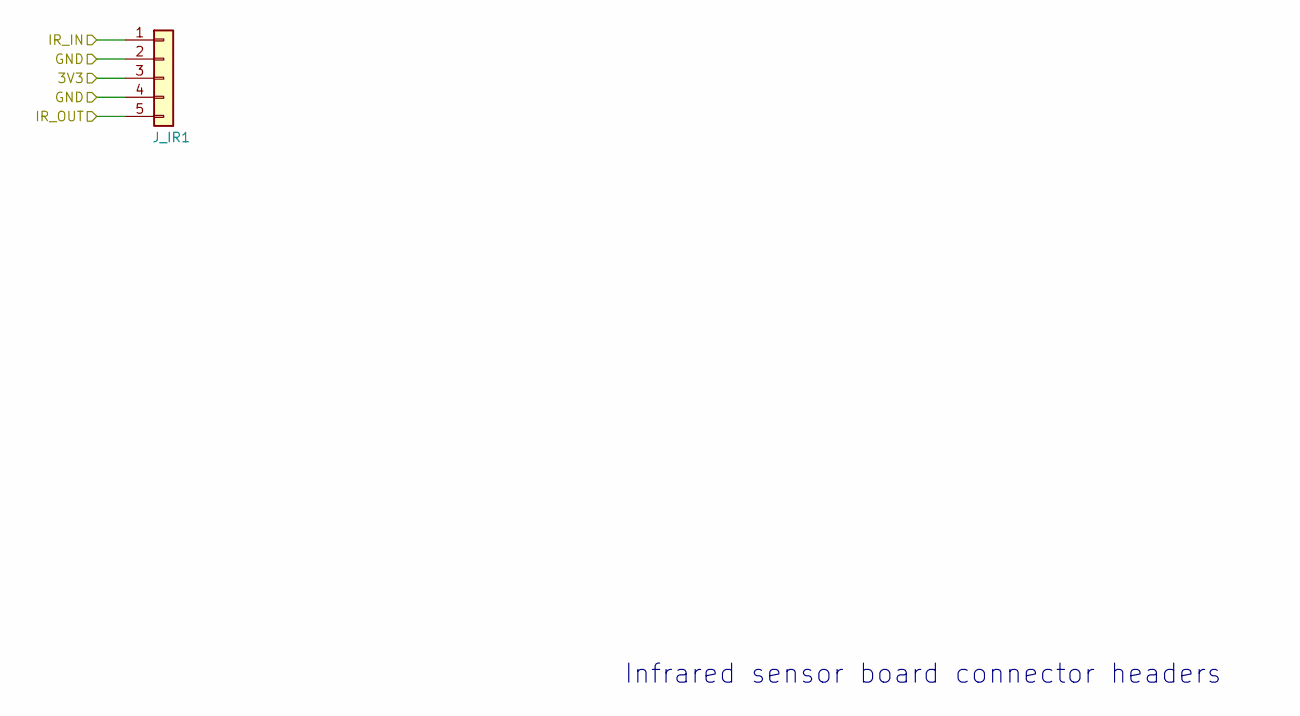
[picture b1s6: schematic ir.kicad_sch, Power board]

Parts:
J_IR1: Connector_Generic:Conn_01x05; PinHeader_1x05_P2.54mm_Vertical_SMD_Pin1Left

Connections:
3V3: J_IR1.3; also elsewhere on the board
/IR/IR_IN: J_IR1.1; also elsewhere on the board
/IR/IR_OUT: J_IR1.5; also elsewhere on the board
GND: J_IR1.2, J_IR1.4; also elsewhere on the board

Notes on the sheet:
Infrared sensor board connector headers
